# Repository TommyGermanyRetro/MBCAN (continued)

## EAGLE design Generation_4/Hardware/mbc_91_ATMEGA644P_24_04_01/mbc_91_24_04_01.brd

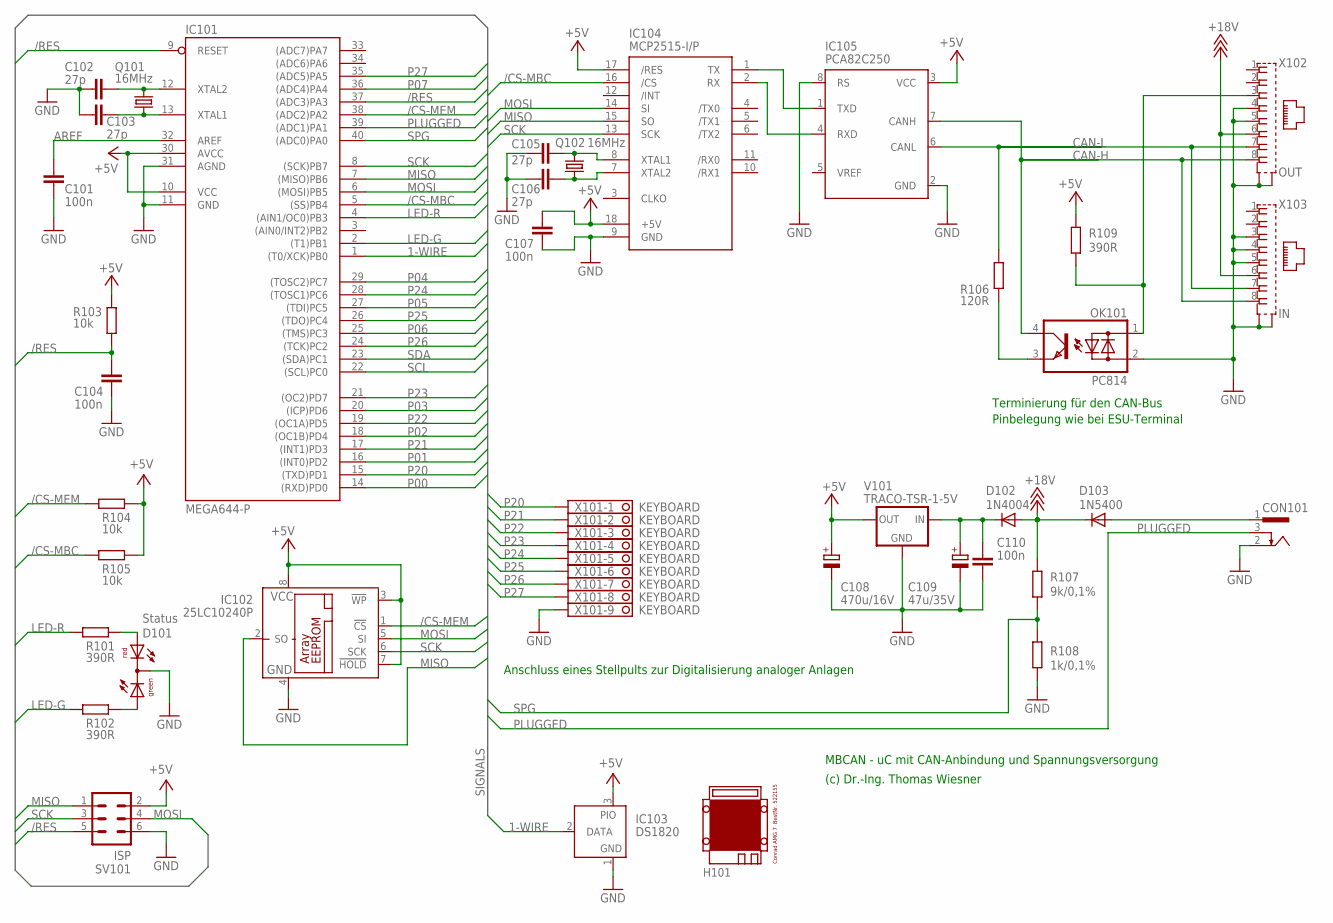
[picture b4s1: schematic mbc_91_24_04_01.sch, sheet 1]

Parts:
C101, C104, C107, C110: 100n; C025-025X050
C102, C103, C105, C106: 27p; C025-025X050
C108: 470u/16V; E3,5-8
C109: 47u/35V; E2,5-7
CON101: POWER-JACK
D101: Status; DUOLED5MM
D102: 1N4004; DO41-10
D103: 1N5400; DO201-15
H101: MODULGEHÄUSE-AMG-7
IC101: MEGA644-P; DIL40
IC102: 25LC10240P; DIL8
IC103: DS1820; TO92-
IC104: MCP2515-I/P; DIL18
IC105: PCA82C250; DIL08
OK101: PC814; DIL04
Q101, Q102: 16MHz; HC49U70
R101, R102, R109: 390R; 0207/10
R103, R104, R105: 10k; 0207/10
R106: 120R; 0207/10
R107: 9k/0,1%; 0207/10
R108: 1k/0,1%; 0207/10
SV101: ISP; ML6
V101: TRACO-TSR-1-5V; TRACO-TSR-1
X101: KEYBOARD; 1751316
X102: OUT; 0446200002
X103: IN; 0446200002

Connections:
1-WIRE: IC101.1 ((T0/XCK)PB0), IC103.2 (DATA)
+5V: C107.1, C108.+, IC101.10 (VCC), IC101.30 (AVCC), IC102.3 (!WP), IC102.7 (!HOLD), IC102.8 (VCC), IC103.3 (PIO), IC104.17 (/RES), IC104.18 (+5V), IC105.3 (VCC), R103.2, R104.2, R105.2, R109.1, SV101.2, V101.OUT; also elsewhere on the board
+18V: D102.A, D103.C, R107.1, X102.6, X103.6; also elsewhere on the board
/CS-MBC: IC101.5 ((SS)PB4), IC104.16 (/CS), R105.1
/CS-MEM: IC101.38 ((ADC2)PA2), IC102.1 (!CS), R104.1
/RES: C104.1, IC101.9 (RESET), IC101.37 ((ADC3)PA3), R103.1, SV101.5
AREF: C101.1, IC101.32 (AREF)
CAN-H: IC105.7 (CANH), OK101.4 (C), X102.8, X103.8
CAN-L: IC105.6 (CANL), R106.2, X102.7, X103.7
GND: C101.2, C102.1, C103.1, C104.2, C105.1, C106.1, C107.2, C108.-, C109.-, C110.2, CON101.2, D101.K (C), IC101.11 (GND), IC101.31 (AGND), IC102.4 (GND), IC103.1 (GND), IC104.9 (GND), IC105.2 (GND), IC105.8 (RS), OK101.2 (AC2), R108.2, SV101.6, V101.GND, X101.9, X102.4, X102.5, X102.S@1 (S1), X102.S@2 (S2), X103.3, X103.4, X103.5, X103.S@1 (S1), X103.S@2 (S2); also elsewhere on the board
LED-G: IC101.2 ((T1)PB1), R102.1
LED-R: IC101.4 ((AIN1/OC0)PB3), R101.1
MISO: IC101.7 ((MISO)PB6), IC102.2 (SO), IC104.15 (SO), SV101.1
MOSI: IC101.6 ((MOSI)PB5), IC102.5 (SI), IC104.14 (SI), SV101.4
unnamed: IC104.1 (TX), IC105.1 (TXD)
unnamed: IC104.2 (RX), IC105.4 (RXD)
unnamed: OK101.3 (E), R106.1
unnamed: OK101.1 (AC1), R109.2, X102.3
unnamed: C109.+, C110.1, D102.C, V101.IN
unnamed: D101.AR, R101.2
unnamed: D101.AG, R102.2
unnamed: C102.2, IC101.12 (XTAL2), Q101.2
unnamed: C103.2, IC101.13 (XTAL1), Q101.1
unnamed: C105.2, IC104.8 (XTAL1), Q102.2
unnamed: C106.2, IC104.7 (XTAL2), Q102.1
P00: IC101.14 ((RXD)PD0); also elsewhere on the board
P01: IC101.16 ((INT0)PD2); also elsewhere on the board
P02: IC101.18 ((OC1B)PD4); also elsewhere on the board
P03: IC101.20 ((ICP)PD6); also elsewhere on the board
P04: IC101.29 ((TOSC2)PC7); also elsewhere on the board
P05: IC101.27 ((TDI)PC5); also elsewhere on the board
P06: IC101.25 ((TMS)PC3); also elsewhere on the board
P07: IC101.36 ((ADC4)PA4); also elsewhere on the board
P20: IC101.15 ((TXD)PD1), X101.1
P21: IC101.17 ((INT1)PD3), X101.2
P22: IC101.19 ((OC1A)PD5), X101.3
P23: IC101.21 ((OC2)PD7), X101.4
P24: IC101.28 ((TOSC1)PC6), X101.5
P25: IC101.26 ((TDO)PC4), X101.6
P26: IC101.24 ((TCK)PC2), X101.7
P27: IC101.35 ((ADC5)PA5), X101.8
PLUGGED: CON101.3, IC101.39 ((ADC1)PA1)
SCK: IC101.8 ((SCK)PB7), IC102.6 (SCK), IC104.13 (SCK), SV101.3
SCL: IC101.22 ((SCL)PC0); also elsewhere on the board
SDA: IC101.23 ((SDA)PC1); also elsewhere on the board
SPG: IC101.40 ((ADC0)PA0), R107.2, R108.1
V-NETZTEIL: CON101.1, D103.A

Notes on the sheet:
MBCAN - uC mit CAN-Anbindung und Spannungsversorgung
(c) Dr.-Ing. Thomas Wiesner
Terminierung für den CAN-Bus
Pinbelegung wie bei ESU-Terminal
Anschluss eines Stellpults zur Digitalisierung analoger Anlagen

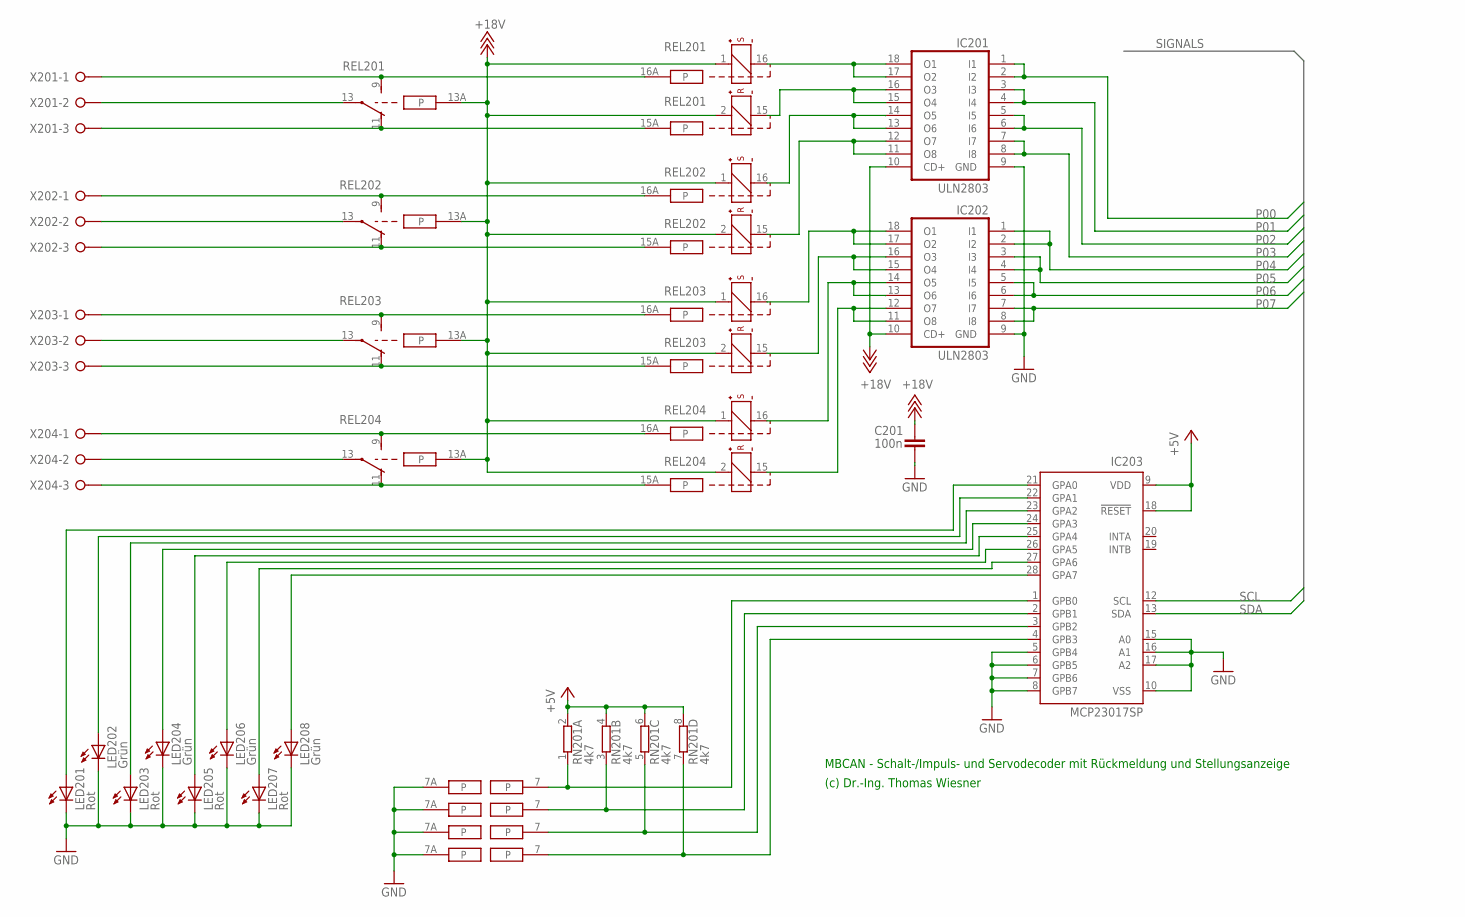
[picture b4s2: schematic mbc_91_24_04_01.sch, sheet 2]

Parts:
C201: 100n; C025-025X050
IC201, IC202: ULN2803; DIL18
IC203: MCP23017SP; DIL28-3
LED201, LED203, LED205, LED207: Rot; LED3MM
LED202, LED204, LED206, LED208: Grün; LED3MM
REL201, REL202, REL203, REL204: RELAIS+PADS; REL-BIPOLAR-LOETPADS
RN201: 4k7; SIL8
X201, X202, X203, X204: W237-03P; W237-133

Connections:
+5V: IC203.9 (VDD), IC203.18 (!RESET), RN201.2, RN201.4 (2), RN201.6 (2), RN201.8 (2); also elsewhere on the board
+18V: C201.1, IC201.10 (CD+), IC202.10 (CD+), REL201.1 (+), REL201.2 (+), REL201.13A, REL202.1 (+), REL202.2 (+), REL202.13A, REL203.1 (+), REL203.2 (+), REL203.13A, REL204.1 (+), REL204.2 (+), REL204.13A; also elsewhere on the board
GND: C201.2, IC201.9 (GND), IC202.9 (GND), IC203.5 (GPB4), IC203.6 (GPB5), IC203.7 (GPB6), IC203.8 (GPB7), IC203.10 (VSS), IC203.15 (A0), IC203.16 (A1), IC203.17 (A2), LED201.K (C), LED202.K (C), LED203.K (C), LED204.K (C), LED205.K (C), LED206.K (C), LED207.K (C), LED208.K (C), REL201.7A, REL202.7A, REL203.7A, REL204.7A; also elsewhere on the board
K11: REL201.9 (S), REL201.16A, X201.1
K12: REL201.13, X201.2
K13: REL201.11 (O), REL201.15A, X201.3
K21: REL202.9 (S), REL202.16A, X202.1
K22: REL202.13, X202.2
K23: REL202.11 (O), REL202.15A, X202.3
K31: REL203.9 (S), REL203.16A, X203.1
K32: REL203.13, X203.2
K33: REL203.11 (O), REL203.15A, X203.3
K41: REL204.9 (S), REL204.16A, X204.1
K42: REL204.13, X204.2
K43: REL204.11 (O), REL204.15A, X204.3
unnamed: IC203.22 (GPA1), LED202.A
unnamed: IC203.21 (GPA0), LED201.A
unnamed: IC201.15 (O4), IC201.16 (O3), REL201.15 (-)
unnamed: IC203.23 (GPA2), LED203.A
unnamed: IC203.25 (GPA4), LED205.A
unnamed: IC203.27 (GPA6), LED207.A
unnamed: IC203.1 (GPB0), REL201.7, RN201.1
unnamed: IC203.2 (GPB1), REL202.7, RN201.3 (1)
unnamed: IC203.3 (GPB2), REL203.7, RN201.5 (1)
unnamed: IC203.4 (GPB3), REL204.7, RN201.7 (1)
unnamed: IC203.24 (GPA3), LED204.A
unnamed: IC203.26 (GPA5), LED206.A
unnamed: IC203.28 (GPA7), LED208.A
unnamed: IC201.11 (O8), IC201.12 (O7), REL202.15 (-)
unnamed: IC202.15 (O4), IC202.16 (O3), REL203.15 (-)
unnamed: IC202.11 (O8), IC202.12 (O7), REL204.15 (-)
P00: IC201.1 (I1), IC201.2 (I2); also elsewhere on the board
P01: IC201.3 (I3), IC201.4 (I4); also elsewhere on the board
P02: IC201.5 (I5), IC201.6 (I6); also elsewhere on the board
P03: IC201.7 (I7), IC201.8 (I8); also elsewhere on the board
P04: IC202.1 (I1), IC202.2 (I2); also elsewhere on the board
P05: IC202.3 (I3), IC202.4 (I4); also elsewhere on the board
P06: IC202.5 (I5), IC202.6 (I6); also elsewhere on the board
P07: IC202.7 (I7), IC202.8 (I8); also elsewhere on the board
S1: IC201.17 (O2), IC201.18 (O1), REL201.16 (-)
S2: IC201.13 (O6), IC201.14 (O5), REL202.16 (-)
S3: IC202.17 (O2), IC202.18 (O1), REL203.16 (-)
S4: IC202.13 (O6), IC202.14 (O5), REL204.16 (-)
SCL: IC203.12 (SCL); also elsewhere on the board
SDA: IC203.13 (SDA); also elsewhere on the board

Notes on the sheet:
MBCAN - Schalt-/Impuls- und Servodecoder mit Rückmeldung und Stellungsanzeige
(c) Dr.-Ing. Thomas Wiesner

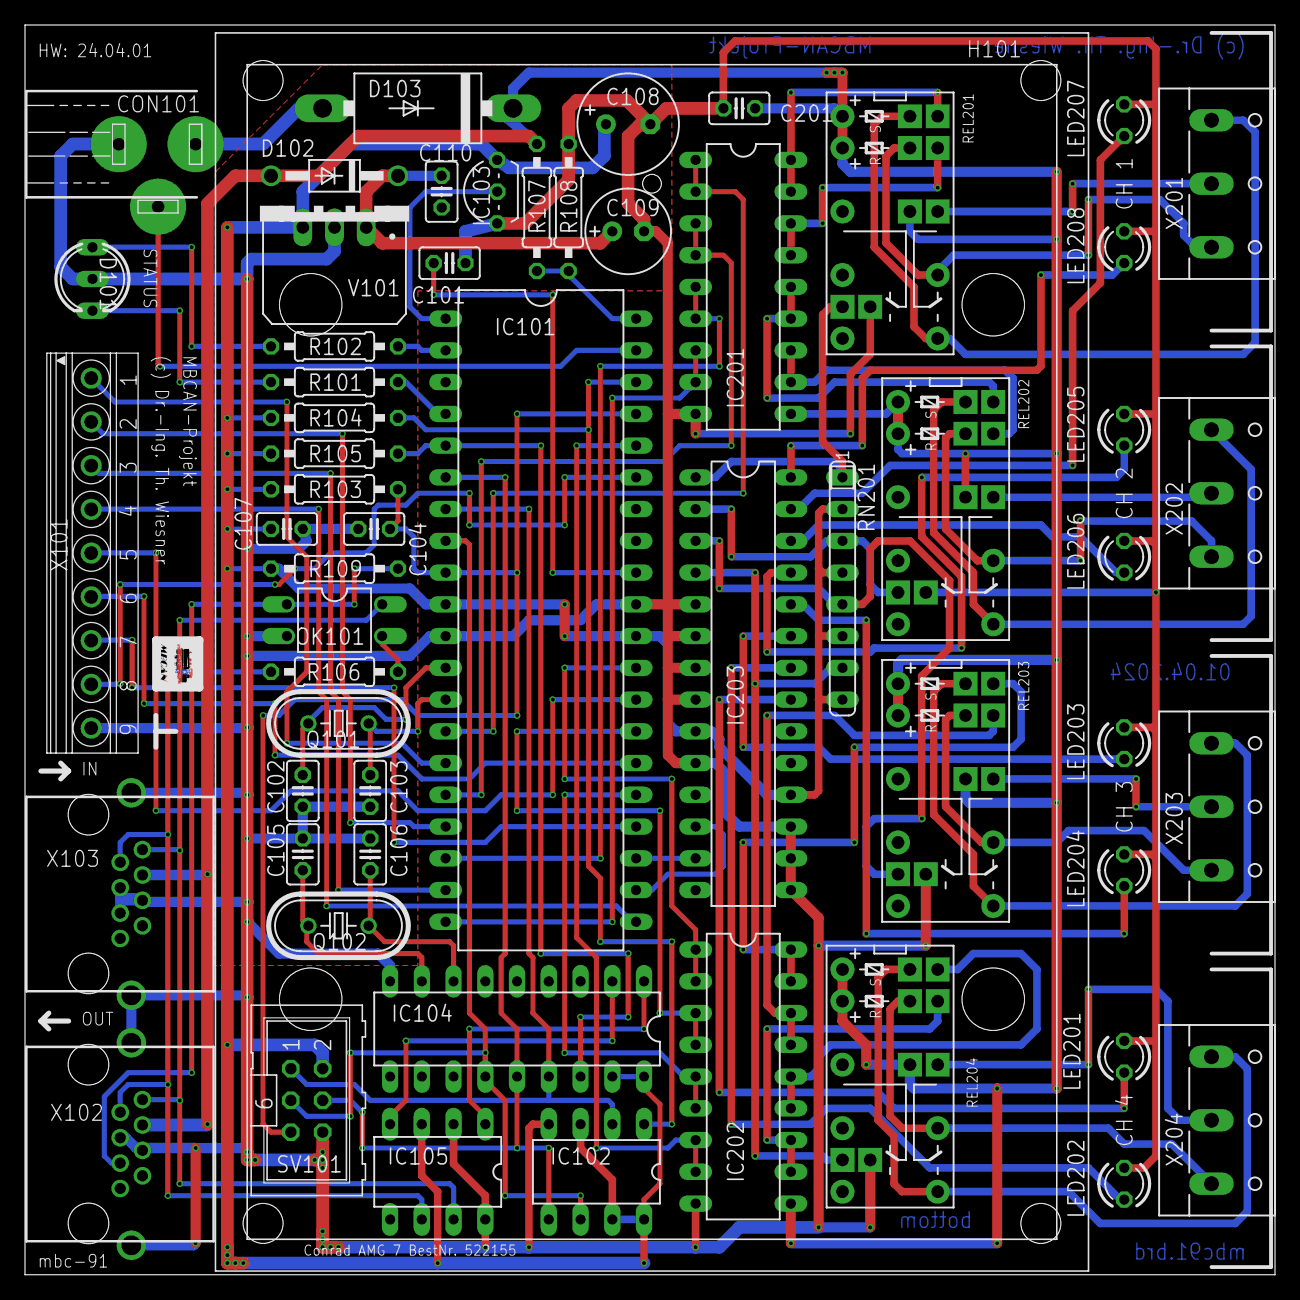
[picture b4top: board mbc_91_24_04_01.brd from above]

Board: 2 copper layers, 100.0 x 100.0 mm, 58 parts (0 on the bottom side), 79 nets.
